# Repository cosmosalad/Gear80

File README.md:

[▶ Check Out GearSeries](https://github.com/cosmosalad/GearSeries)<br/>
[자작 과정(kr)](https://blog.naver.com/cosmosalad/223262540878)<br/><br/>

# Gear80<br/>
Gear80 is a 80% keyboard based on the rp2040.

<br/>

- gear80_wkl_Aluminum (CNC, Bead blasting-100 mesh + Anodizing-Black-Matte)

<p align="center">

</p>

<br/>

- gear80_wkl (sla print)

<br/>

- Gear80-A_1.0mm (sla print)

<br/><br/>

## Layout<br/>

- gear80 hotswap, solder

<br/>
<br/>

- gear80-a solder
<br/>
<br/>

<br/>

There is also a [keyboard plate](https://github.com/cosmosalad/Gear80/tree/main/plate).<br/>
[Keyboard case](https://github.com/cosmosalad/Gear80/tree/main/case) corresponding to this layout.<br/>

<br/><br/>

## PCB<br/>
It may differ from the sample photo and file.<br/>
<br/>
<br/>

<br/>

<br/>
<br/>
[More pcb ](https://github.com/cosmosalad/Gear80/tree/main/pcb)<br/>

This pcb was made by jlcpcb.(list of pcb parts [main](https://github.com/cosmosalad/Gear80/blob/main/pcb/Gear80%20solder/part%20list.md), [daughterboard](https://github.com/cosmosalad/Gear80/blob/main/pcb/daughterboard/part%20list.md/))<br/><br/>

This pcb prepared the [vial](https://github.com/cosmosalad/Gear80/tree/main/vial) as firmware<br/><br/><br/>

## typing sound<br/>
<p align="center">

  <br/>
Gear80 / Aluminum / HMX Hyacinth v2u / PC Plate / ABS / Full foam
<br/><br/>

  <br/>
Gear80 / Aluminum / HMX Garnet / PC Plate / ABS / no foam
<br/><br/>
  
  <br/>
Gear80 Lite / Bsun RAW /  PC Plate / ABS / Full foam
<br/><br/>
  
  <br/>
Gear80-A / sla / HMX Cheese / PC Plate / PBT / Full foam
<br/><br/>

</p>
<br/>

## Reference<br/>
- [Gear60](https://github.com/cosmosalad/Gear60)
<br/>

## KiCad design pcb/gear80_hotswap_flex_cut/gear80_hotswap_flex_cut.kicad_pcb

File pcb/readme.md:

### Gear80 hotswap<br/>
<br/>
<br/>

<br/><br/>

### Gear80 solder<br/>
<br/>
<br/>

<br/><br/>

### Gear80-A_1.0mm<br/>
<br/>
<br/>

<br/><br/>

### Gear80-A_0.5mm<br/>
<br/>
<br/>

<br/><br/>

### Gear80-daughterboard ver.0.1, ver.0.2<br/>
<br/>
<br/>

<br/><br/>

### Gear80 hotswap flex cut<br/>
<br/>
<br/>

<br/><br/>

### Gear85 hotswap flex cut, number pad<br/>
<br/>
<br/>

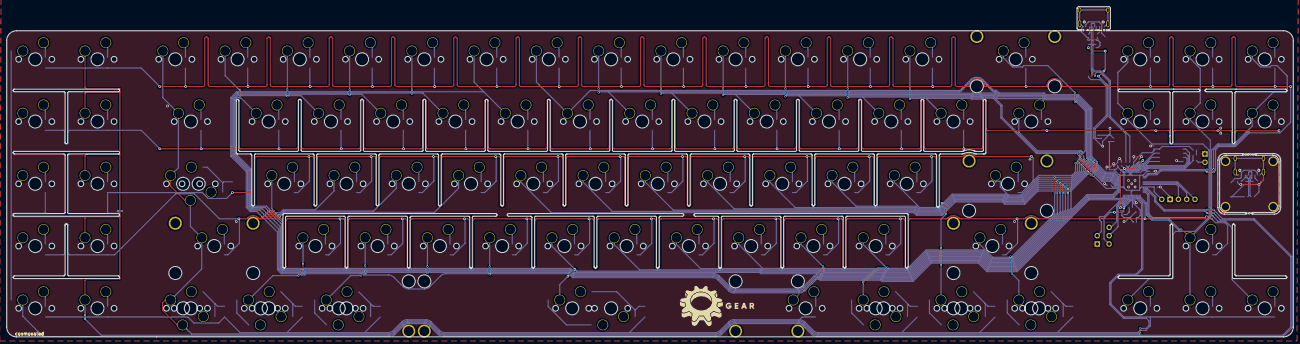
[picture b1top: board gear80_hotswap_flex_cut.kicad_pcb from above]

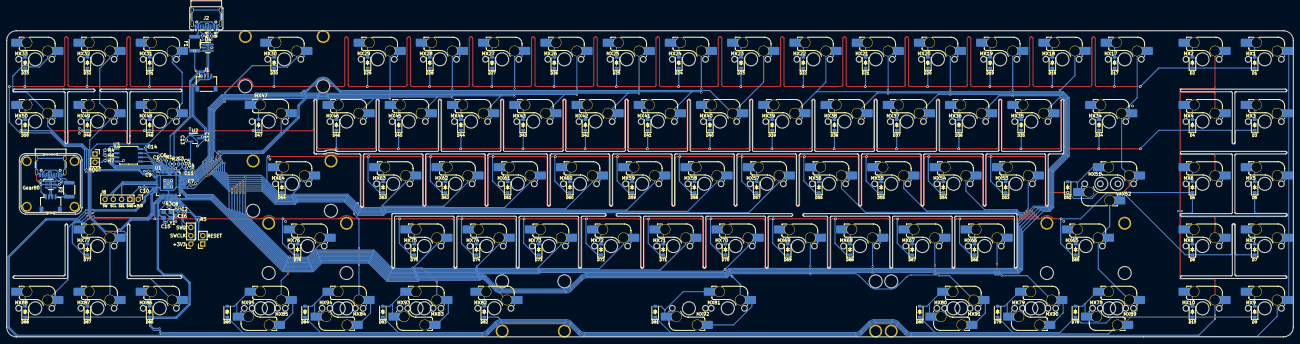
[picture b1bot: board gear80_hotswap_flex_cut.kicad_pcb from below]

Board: 2 copper layers, 393.7 x 101.0 mm, 220 parts (212 on the bottom side), 140 nets.

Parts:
BOOT1: SW_Push; PinSocket_1x02_P2.54mm_Vertical
C1, C2, C4, C5, C6, C7, C8, C9, C10: 100n; C_0402_1005Metric
C3, C11, C12, C13, C14: 1u; C_0402_1005Metric
C15, C16: 22p; C_0402_1005Metric
D1, D2, D3, D4, D5, D6, D7, D8, D9, D10, D17, D18, D19, D20, D21, D22, D23, D24, D25, D26, D27, D28, D29, D30, D31, D32, D33, D34, D35, D36, D37, D38, D39, D40, D41, D42, D43, D44, D45, D46, D47, D48, D49, D50, D51, D53, D54, D55, D56, D57, D58, D59, D60, D61, D62, D63, D64, D65, D66, D67, D68, D69, D70, D71, D72, D73, D74, D75, D76, D77, D78, D79, D80, D81, D82, D83, D84, D85, D86, D87, D88: D_Small; D_SOD-123_new
F1, F2: MF-MSMF050-2; Fuse_1812_4532Metric
GEAR: LOGO
J1, J4: Conn_01x04; JST_SH_SM04B-SRSS-TB_1x04-1MP_P1.00mm_Horizontal
J2, J5: USB_C_Receptacle_USB2.0; USB_C_Receptacle_HRO_TYPE-C-31-M-12
J3: SWD; PinSocket_1x03_P2.54mm_Vertical
J8: Conn_01x05; PinSocket_1x05_P2.54mm_Vertical
MX1, MX2, MX3, MX4, MX5, MX6, MX7, MX8, MX9, MX10, MX17, MX18, MX19, MX20, MX21, MX22, MX23, MX24, MX25, MX26, MX27, MX28, MX29, MX30, MX31, MX32, MX33, MX35, MX36, MX37, MX38, MX39, MX40, MX41, MX42, MX43, MX44, MX45, MX46, MX48, MX49, MX50, MX53, MX54, MX55, MX56, MX57, MX58, MX59, MX60, MX61, MX62, MX63, MX64, MX65, MX66, MX67, MX68, MX69, MX70, MX71, MX72, MX73, MX74, MX75, MX76, MX77, MX81, MX86, MX87, MX88, MX90, MX92, MX94: MX_SW_HS; SW_MX_HS_1u
MX34, MX47, MX89, MX91, MX93, MX95: MX_SW_HS; SW_MX_HS_1.5u
MX51: MX_SW_HS; SW_MX_HS_1.75u_STP_1.25
MX52: MX_SW_HS; SW_MX_HS_1.75u
MX78, MX79, MX80, MX82, MX83, MX84, MX85: MX_SW_HS; SW_MX_HS_1.25u
R1, R2: 27; R_0402_1005Metric
R3, R7: 1k; R_0402_1005Metric
R4, R5, R6, R8, R9, R10, R11: 5.1k; R_0402_1005Metric
RESET1: SW_Push; PinSocket_1x02_P2.54mm_Vertical
S1: stb; STAB_MX_P_2u
S3, S4: stb; STAB_MX_P_2.25u
S5: stb; STAB_MX_P_2.75u
S6: stb; STAB_MX_P_7u
S7: stb; STAB_MX_P_6.25u
U1: RP2040; QFN-56-1EP_7x7mm_P0.4mm_EP3.2x3.2mm
U2: XC6206P332MR; SOT-23-3
U3: W25Q128JVSIQ; SOIC-8_5.23x5.23mm_P1.27mm
U4, U5: SRV05-4; SOT-23-6-routable
Y1: X322512MSB4SI; Crystal_SMD_3225-4Pin_3.2x2.5mm

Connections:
+1V1: C1.1, C2.1, C3.1, U1.23 (DVDD), U1.45 (VREG_VOUT), U1.50 (DVDD)
+3V3: C4.1, C5.1, C6.1, C7.1, C8.1, C9.1, C10.1, C11.1, C13.1, C14.1, J3.1, J8.1, R4.2, R5.2, U1.1 (IOVDD), U1.10 (IOVDD), U1.22 (IOVDD), U1.33 (IOVDD), U1.42 (IOVDD), U1.43 (ADC_AVDD), U1.44 (VREG_IN), U1.48 (USB_VDD), U1.49 (IOVDD), U2.2 (VO), U3.8 (VCC)
+5V: C12.1, F1.1, J1.1, U2.3 (VI), U4.5 (VP)
+5VA: F2.1, J4.4, U5.5 (VP)
COL0: MX1.1, MX3.1, MX5.1, MX7.1, MX9.1, U1.11 (GPIO8)
COL1: MX2.1, MX4.1, MX6.1, MX8.1, MX10.1, U1.12 (GPIO9)
COL2: MX17.1, MX34.1, MX51.1, MX52.2, MX65.1, MX78.1, MX89.2, U1.18 (GPIO15)
COL3: MX18.1, MX35.1, U1.31 (GPIO20)
COL4: MX19.1, MX36.1, MX53.1, MX66.1, MX79.1, MX90.2, U1.30 (GPIO19)
COL5: MX20.1, MX37.1, MX54.1, MX67.1, MX80.1, MX91.2, U1.29 (GPIO18)
COL6: MX21.1, MX38.1, MX55.1, MX68.1, U1.28 (GPIO17)
COL7: MX22.1, MX39.1, MX56.1, MX69.1, U1.27 (GPIO16)
COL8: MX23.1, MX40.1, MX57.1, MX70.1, MX81.1, MX92.2, U1.41 (GPIO29_ADC3)
COL9: MX24.1, MX41.1, MX58.1, MX71.1, U1.40 (GPIO28_ADC2)
COL10: MX25.1, MX42.1, MX59.1, MX72.1, U1.39 (GPIO27_ADC1)
COL11: MX26.1, MX43.1, MX60.1, MX73.1, U1.38 (GPIO26_ADC0)
COL12: MX27.1, MX44.1, MX61.1, MX74.1, MX82.1, U1.37 (GPIO25)
COL13: MX28.1, MX45.1, MX62.1, MX75.1, MX83.2, MX93.1, U1.36 (GPIO24)
COL14: MX29.1, MX46.1, MX63.1, MX84.2, MX94.1, U1.35 (GPIO23)
COL15: MX30.1, MX47.1, MX64.1, MX76.1, MX85.2, MX95.1, U1.34 (GPIO22)
COL16: MX31.1, MX48.1, MX86.1, U1.15 (GPIO12)
COL17: MX32.1, MX49.1, MX77.1, MX87.1, U1.14 (GPIO11)
COL18: MX33.1, MX50.1, MX88.1, U1.13 (GPIO10)
GND: BOOT1.1, C1.2, C2.2, C3.2, C4.2, C5.2, C6.2, C7.2, C8.2, C9.2, C10.2, C11.2, C12.2, C13.2, C14.2, C15.1, C16.1, J1.4, J2.A1 (GND), J2.A12 (GND), J2.B1 (GND), J2.B12 (GND), J2.S1 (SHIELD), J8.2, R8.2, R9.2, RESET1.1, U1.19 (TESTEN), U1.57 (GND), U2.1 (GND), U3.4 (GND), U4.2 (VN), Y1.2, Y1.4
GNDA: J4.1, J5.A1 (GND), J5.A12 (GND), J5.B1 (GND), J5.B12 (GND), J5.S1 (SHIELD), R10.2, R11.2, U5.2 (VN)
GP_SCL: J8.4, U1.7 (GPIO5)
GP_SDA: J8.3, U1.8 (GPIO6)
unnamed: BOOT1.2, R7.1
unnamed: C16.2, R3.1, Y1.1
unnamed: D1.2 (A), MX1.2
unnamed: D2.2 (A), MX2.2
unnamed: D3.2 (A), MX3.2
unnamed: D4.2 (A), MX4.2
unnamed: D5.2 (A), MX5.2
unnamed: D6.2 (A), MX6.2
unnamed: D7.2 (A), MX7.2
unnamed: D8.2 (A), MX8.2
unnamed: D9.2 (A), MX9.2
unnamed: D10.2 (A), MX10.2
unnamed: D17.2 (A), MX17.2
unnamed: D18.2 (A), MX18.2
unnamed: D19.2 (A), MX19.2
unnamed: D20.2 (A), MX20.2
unnamed: D21.2 (A), MX21.2
unnamed: D22.2 (A), MX22.2
unnamed: D23.2 (A), MX23.2
unnamed: D24.2 (A), MX24.2
unnamed: D25.2 (A), MX25.2
unnamed: D26.2 (A), MX26.2
unnamed: D27.2 (A), MX27.2
unnamed: D28.2 (A), MX28.2
unnamed: D29.2 (A), MX29.2
unnamed: D30.2 (A), MX30.2
unnamed: D31.2 (A), MX31.2
unnamed: D32.2 (A), MX32.2
unnamed: D33.2 (A), MX33.2
unnamed: D34.2 (A), MX34.2
unnamed: D35.2 (A), MX35.2
unnamed: D36.2 (A), MX36.2
unnamed: D37.2 (A), MX37.2
unnamed: D38.2 (A), MX38.2
unnamed: D39.2 (A), MX39.2
unnamed: D40.2 (A), MX40.2
unnamed: D41.2 (A), MX41.2
unnamed: D42.2 (A), MX42.2
unnamed: D43.2 (A), MX43.2
unnamed: D44.2 (A), MX44.2
unnamed: D45.2 (A), MX45.2
unnamed: D46.2 (A), MX46.2
unnamed: D47.2 (A), MX47.2
unnamed: D48.2 (A), MX48.2
unnamed: D49.2 (A), MX49.2
unnamed: D50.2 (A), MX50.2
unnamed: D51.2 (A), MX51.2, MX52.1
unnamed: D53.2 (A), MX53.2
unnamed: D54.2 (A), MX54.2
unnamed: D55.2 (A), MX55.2
unnamed: D56.2 (A), MX56.2
unnamed: D57.2 (A), MX57.2
unnamed: D58.2 (A), MX58.2
unnamed: D59.2 (A), MX59.2
unnamed: D60.2 (A), MX60.2
unnamed: D61.2 (A), MX61.2
unnamed: D62.2 (A), MX62.2
unnamed: D63.2 (A), MX63.2
unnamed: D64.2 (A), MX64.2
unnamed: D65.2 (A), MX65.2
unnamed: D66.2 (A), MX66.2
unnamed: D67.2 (A), MX67.2
unnamed: D68.2 (A), MX68.2
unnamed: D69.2 (A), MX69.2
unnamed: D70.2 (A), MX70.2
unnamed: D71.2 (A), MX71.2
unnamed: D72.2 (A), MX72.2
unnamed: D73.2 (A), MX73.2
unnamed: D74.2 (A), MX74.2
unnamed: D75.2 (A), MX75.2
unnamed: D76.2 (A), MX76.2
unnamed: D77.2 (A), MX77.2
unnamed: D78.2 (A), MX78.2, MX89.1
unnamed: D79.2 (A), MX79.2, MX90.1
unnamed: D80.2 (A), MX80.2, MX91.1
unnamed: D81.2 (A), MX81.2, MX92.1
unnamed: D82.2 (A), MX82.2
unnamed: D83.2 (A), MX83.1, MX93.2
unnamed: D84.2 (A), MX84.1, MX94.2
unnamed: D85.2 (A), MX85.1, MX95.2
unnamed: D86.2 (A), MX86.2
unnamed: D87.2 (A), MX87.2
unnamed: D88.2 (A), MX88.2
unnamed: J2.A5 (CC1), R8.1
unnamed: J2.B5 (CC2), R9.1
unnamed: J5.A5 (CC1), R10.1
unnamed: J5.B5 (CC2), R11.1
unnamed: R4.1, R6.2
unnamed: R2.2, U1.46 (USB_DM)
unnamed: R1.2, U1.47 (USB_DP)
QSPI_SCLK: U1.52 (QSPI_SCLK), U3.6 (CLK)
QSPI_SD0: U1.53 (QSPI_SD0), U3.5 (DI(IO0))
QSPI_SD1: U1.55 (QSPI_SD1), U3.2 (DO(IO1))
QSPI_SD2: U1.54 (QSPI_SD2), U3.3 (IO2)
QSPI_SD3: U1.51 (QSPI_SD3), U3.7 (IO3)
QSPI_SS: R6.1, R7.2, U1.56 (QSPI_SS), U3.1 (~CS)
RESET: R5.1, RESET1.2, U1.26 (RUN)
ROW0: D1.1 (K), D2.1 (K), D17.1 (K), D18.1 (K), D19.1 (K), D20.1 (K), D21.1 (K), D22.1 (K), D23.1 (K), D24.1 (K), D25.1 (K), D26.1 (K), D27.1 (K), D28.1 (K), D29.1 (K), D30.1 (K), D31.1 (K), D32.1 (K), D33.1 (K), U1.3 (GPIO1)
ROW1: D3.1 (K), D4.1 (K), D34.1 (K), D35.1 (K), D36.1 (K), D37.1 (K), D38.1 (K), D39.1 (K), D40.1 (K), D41.1 (K), D42.1 (K), D43.1 (K), D44.1 (K), D45.1 (K), D46.1 (K), D47.1 (K), D48.1 (K), D49.1 (K), D50.1 (K), U1.2 (GPIO0)
ROW2: D5.1 (K), D6.1 (K), D51.1 (K), D53.1 (K), D54.1 (K), D55.1 (K), D56.1 (K), D57.1 (K), D58.1 (K), D59.1 (K), D60.1 (K), D61.1 (K), D62.1 (K), D63.1 (K), D64.1 (K), U1.32 (GPIO21)
ROW3: D7.1 (K), D8.1 (K), D65.1 (K), D66.1 (K), D67.1 (K), D68.1 (K), D69.1 (K), D70.1 (K), D71.1 (K), D72.1 (K), D73.1 (K), D74.1 (K), D75.1 (K), D76.1 (K), D77.1 (K), U1.16 (GPIO13)
ROW4: D9.1 (K), D10.1 (K), D78.1 (K), D79.1 (K), D80.1 (K), D81.1 (K), D82.1 (K), D83.1 (K), D84.1 (K), D85.1 (K), D86.1 (K), D87.1 (K), D88.1 (K), U1.17 (GPIO14)
SW: J8.5, U1.6 (GPIO4)
SWCLK: J3.2, U1.24 (SWCLK)
SWD: J3.3, U1.25 (SWD)
USB_D+: J1.3, J2.A6 (D+), J2.B6 (D+), R1.1, U4.1 (IO1)
USB_D+_DB: J4.2, J5.A6 (D+), J5.B6 (D+), U5.1 (IO1)
USB_D-: J1.2, J2.A7 (D-), J2.B7 (D-), R2.1, U4.6 (IO4)
USB_D-_DB: J4.3, J5.A7 (D-), J5.B7 (D-), U5.6 (IO4)
VBUS: F1.2, J2.A4 (VBUS), J2.A9 (VBUS), J2.B4 (VBUS), J2.B9 (VBUS)
VCC: F2.2, J5.A4 (VBUS), J5.A9 (VBUS), J5.B4 (VBUS), J5.B9 (VBUS)
XIN: C15.2, U1.20 (XIN), Y1.3
XOUT: R3.2, U1.21 (XOUT)

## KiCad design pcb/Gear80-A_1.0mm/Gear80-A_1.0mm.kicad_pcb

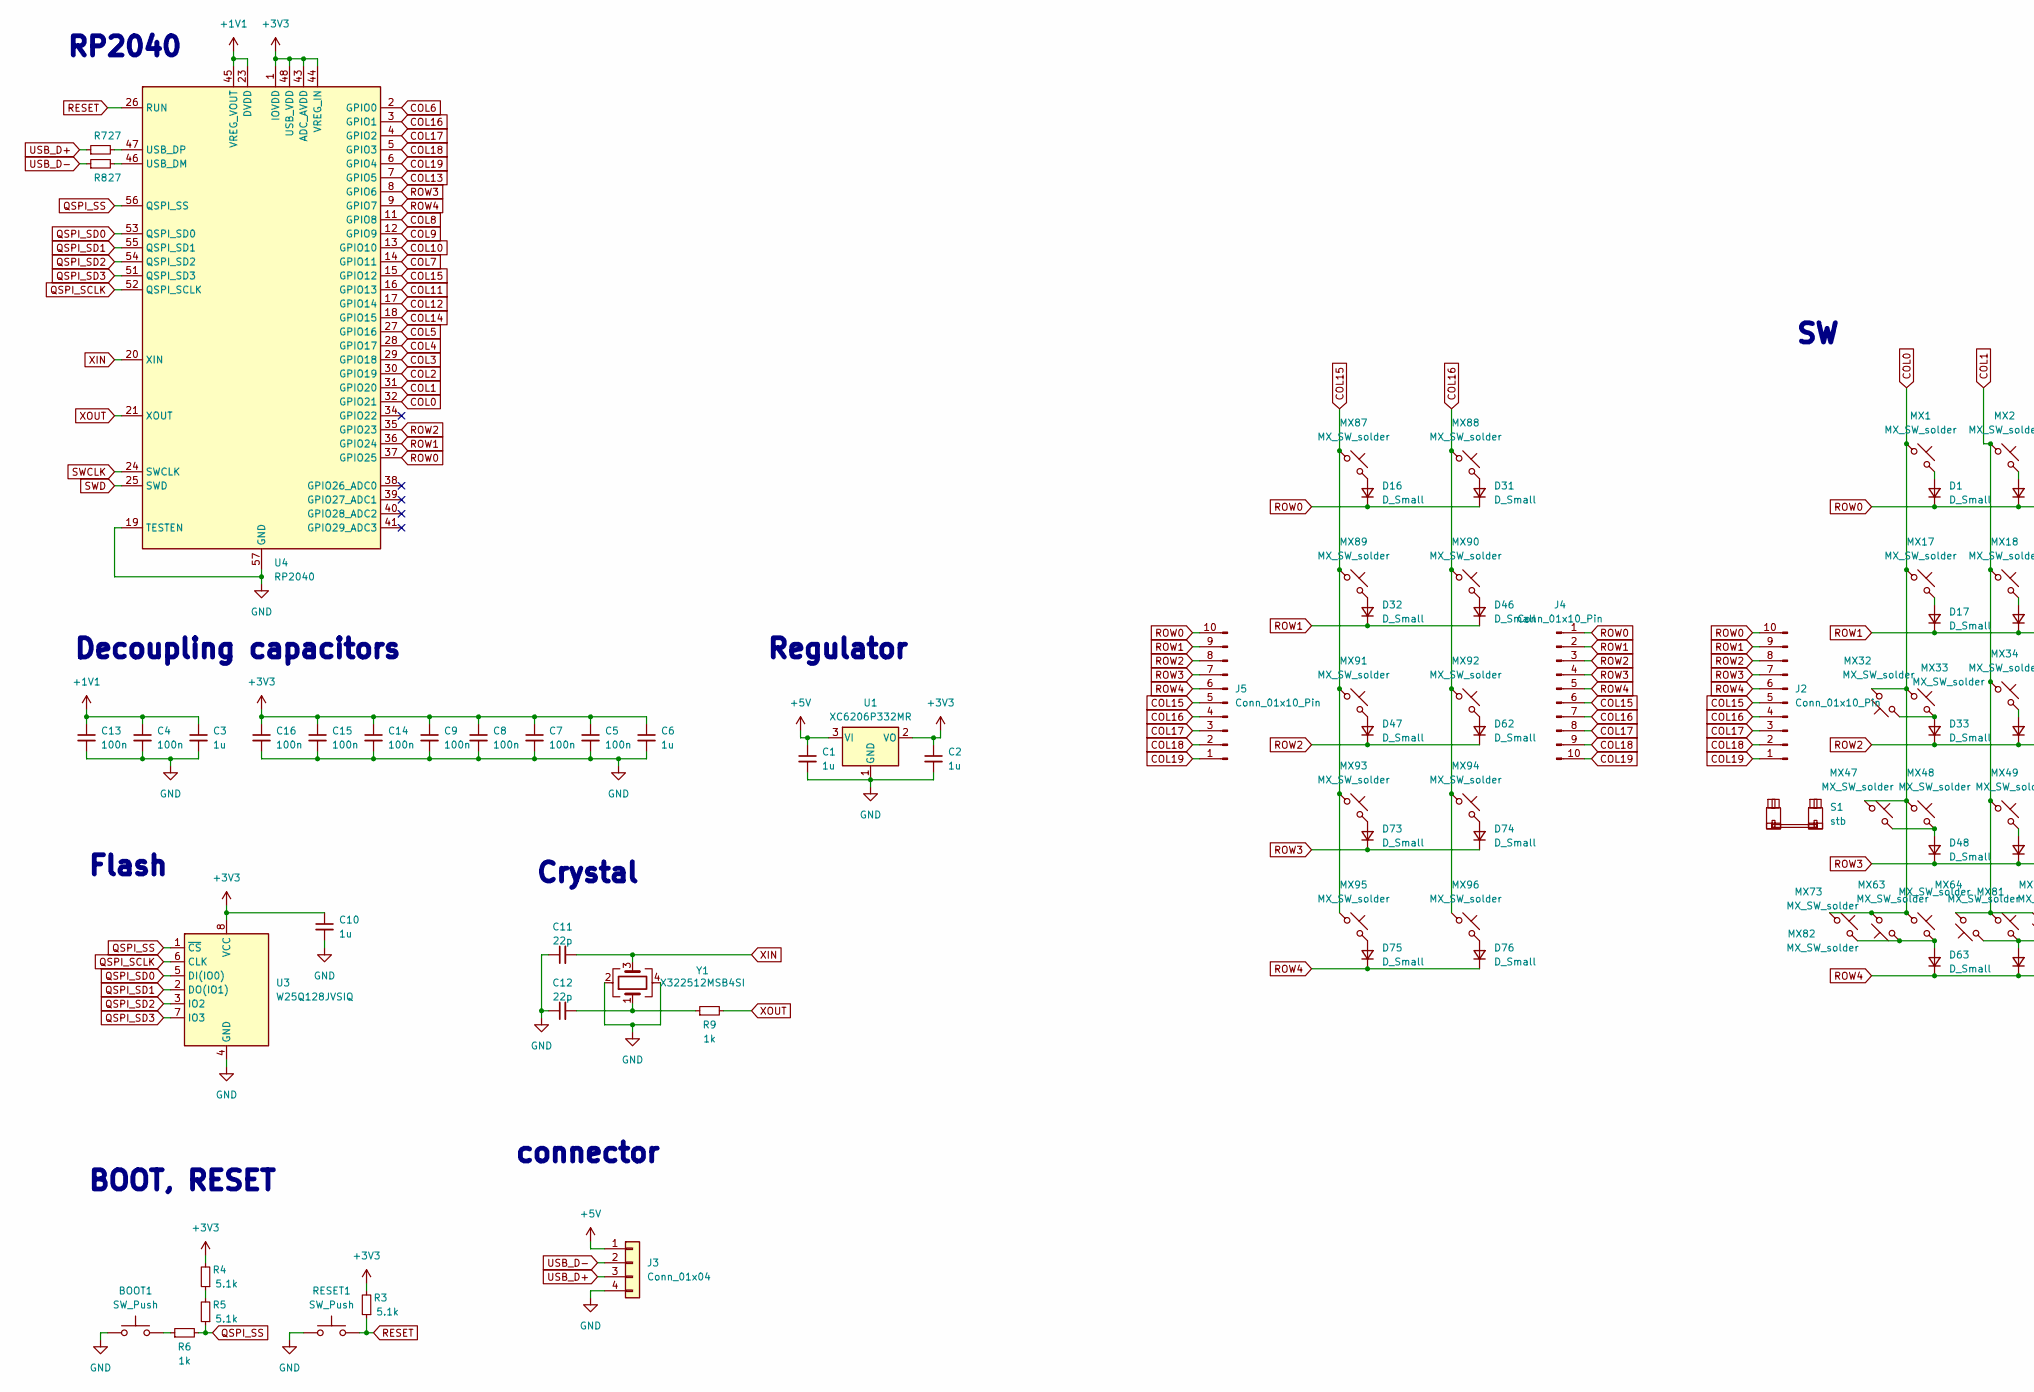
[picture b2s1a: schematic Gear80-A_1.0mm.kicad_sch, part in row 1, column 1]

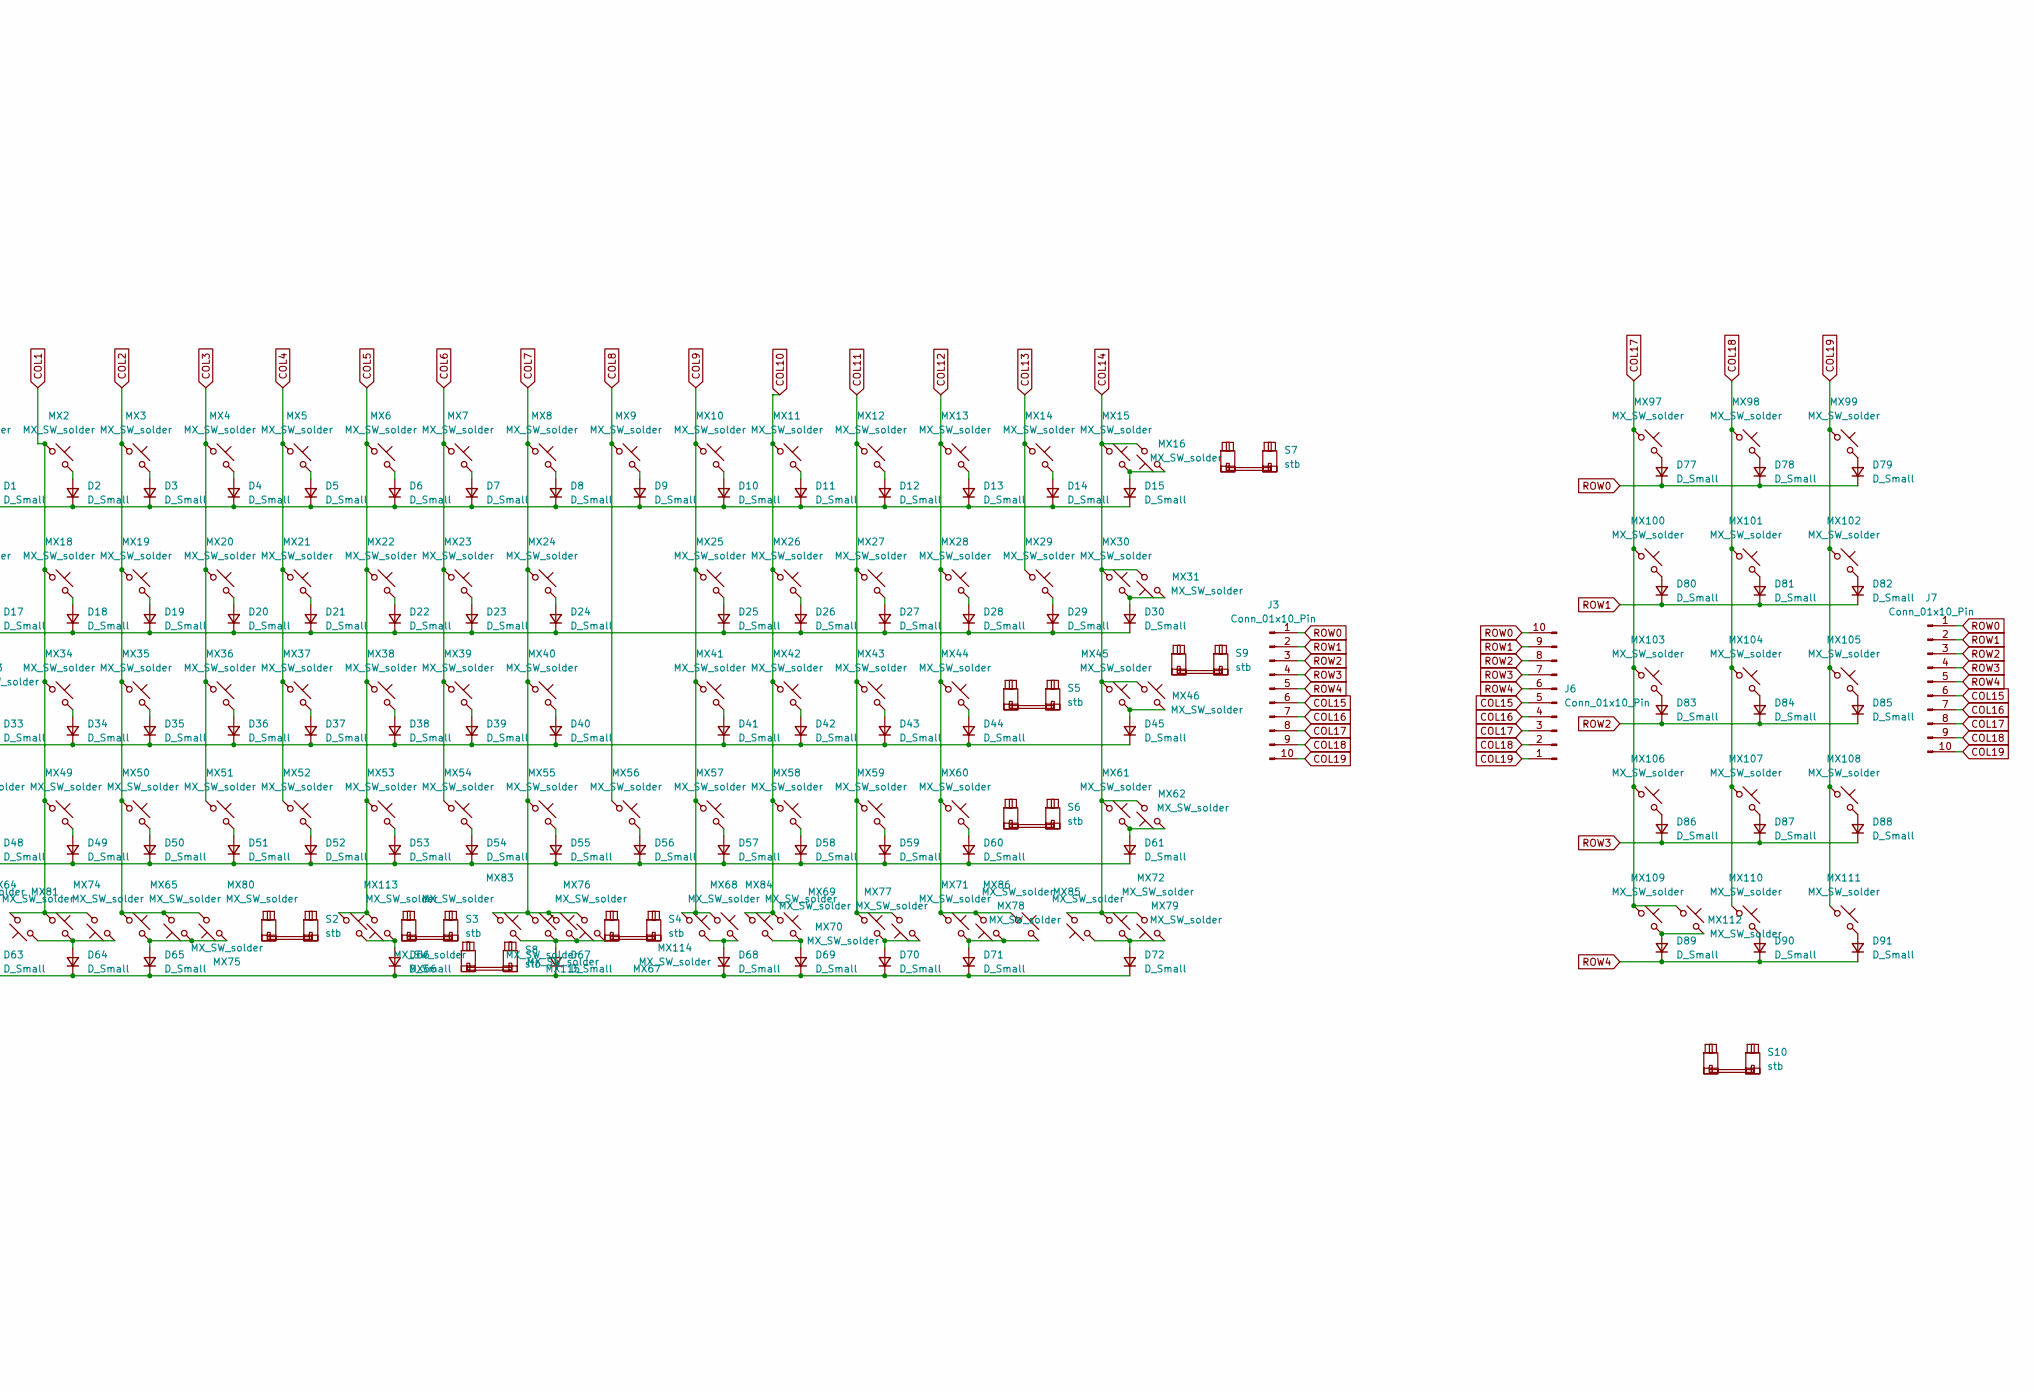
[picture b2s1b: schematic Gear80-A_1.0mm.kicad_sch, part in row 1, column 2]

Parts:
BOOT1: SW_Push; PinSocket_1x02_P2.54mm_Vertical
C1, C2, C3, C6, C10: 1u; C_0402_1005Metric
C4, C5, C7, C8, C9, C13, C14, C15, C16: 100n; C_0402_1005Metric
C11, C12: 22p; C_0402_1005Metric
D1, D2, D3, D4, D5, D6, D7, D8, D9, D10, D11, D12, D13, D14, D15, D16, D17, D18, D19, D20, D21, D22, D23, D24, D25, D26, D27, D28, D29, D30, D31, D32, D33, D34, D35, D36, D37, D38, D39, D40, D41, D42, D43, D44, D45, D46, D47, D48, D49, D50, D51, D52, D53, D54, D55, D56, D57, D58, D59, D60, D61, D62, D63, D64, D65, D66, D67, D68, D69, D70, D71, D72, D73, D74, D75, D76, D77, D78, D79, D80, D81, D82, D83, D84, D85, D86, D87, D88, D89, D90, D91: D_Small; D_SOD-123
J2, J3, J4, J5, J6, J7: Conn_01x10_Pin; Molex_200528-0100_1x10-1MP_P1.00mm_Horizontal
MX1, MX2, MX3, MX4, MX5, MX6, MX7, MX8, MX9, MX10, MX11, MX12, MX13, MX14, MX15, MX16, MX18, MX19, MX20, MX21, MX22, MX23, MX24, MX25, MX26, MX27, MX28, MX29, MX31, MX34, MX35, MX36, MX37, MX38, MX39, MX40, MX41, MX42, MX43, MX44, MX45, MX46, MX47, MX49, MX50, MX51, MX52, MX53, MX54, MX55, MX56, MX57, MX58, MX59, MX61, MX62, MX63, MX64, MX66, MX67, MX69, MX70, MX71, MX72, MX74, MX76, MX78, MX83, MX87, MX88, MX89, MX90, MX91, MX92, MX93, MX94, MX95, MX96, MX97, MX98, MX99, MX100, MX101, MX102, MX103, MX104, MX105, MX106, MX107, MX108, MX109, MX110, MX111, MX112, MX113, MX114, MX115: MX_SW_solder; SW_MX_1u
MX17, MX30, MX73, MX75, MX79: MX_SW_solder; SW_MX_1.5u
MX32: MX_SW_solder; SW_MX_1.75u_STP_1.25
MX33, MX60: MX_SW_solder; SW_MX_1.75u
MX48, MX65, MX68, MX77, MX80, MX81, MX82, MX84, MX85, MX86: MX_SW_solder; SW_MX_1.25u
R3, R4, R5: 5.1k; R_0402_1005Metric
R6, R9: 1k; R_0402_1005Metric
R7, R8: 27; R_0402_1005Metric
RESET1: SW_Push; PinSocket_1x02_P2.54mm_Vertical
S1, S3, S5: stb; STAB_MX_P_2.25u
S2, S6: stb; STAB_MX_P_2.75u
S4: stb; STAB_MX_P_7u
S7, S10: stb; STAB_MX_P_2u
S8: stb; STAB_MX_P_6.25u
S9: stb; STAB_MX_ISO
U1: XC6206P332MR; SOT-23-3
U3: W25Q128JVSIQ; SOIC-8_5.23x5.23mm_P1.27mm
U4: RP2040; QFN-56-1EP_7x7mm_P0.4mm_EP3.2x3.2mm
Y1: X322512MSB4SI; Crystal_SMD_3225-4Pin_3.2x2.5mm

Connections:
+1V1: C3.1, C4.1, C13.1, U4.23 (DVDD), U4.45 (VREG_VOUT), U4.50 (DVDD)
+3V3: C2.1, C5.1, C6.1, C7.1, C8.1, C9.1, C10.1, C14.1, C15.1, C16.1, R3.2, R4.2, U1.2 (VO), U3.8 (VCC), U4.1 (IOVDD), U4.10 (IOVDD), U4.22 (IOVDD), U4.33 (IOVDD), U4.42 (IOVDD), U4.43 (ADC_AVDD), U4.44 (VREG_IN), U4.48 (USB_VDD), U4.49 (IOVDD)
COL0: MX1.1, MX17.1, MX32.2, MX33.1, MX47.1, MX48.1, MX63.1, MX73.2, MX82.1, U4.32 (GPIO21)
COL1: MX2.1, MX18.1, MX34.1, MX49.1, MX64.1, MX74.2, MX81.2, U4.31 (GPIO20)
COL2: MX3.1, MX19.1, MX35.1, MX50.1, MX65.1, MX75.2, MX80.2, U4.30 (GPIO19)
COL3: MX4.1, MX20.1, MX36.1, MX51.1, U4.29 (GPIO18)
COL4: MX5.1, MX21.1, MX37.1, MX52.1, U4.28 (GPIO17)
COL5: MX6.1, MX22.1, MX38.1, MX53.1, MX66.2, MX113.1, U4.27 (GPIO16)
COL6: MX7.1, MX23.1, MX39.1, MX54.1, U4.2 (GPIO0)
COL7: MX8.1, MX24.1, MX40.1, MX55.1, MX67.1, MX76.1, MX83.1, MX115.2, U4.14 (GPIO11)
COL8: MX9.1, MX56.1, U4.11 (GPIO8)
COL9: MX10.1, MX25.1, MX41.1, MX57.1, MX68.1, MX114.1, U4.12 (GPIO9)
COL10: MX11.1, MX26.1, MX42.1, MX58.1, MX69.1, MX84.1, U4.13 (GPIO10)
COL11: MX12.1, MX27.1, MX43.1, MX59.1, MX70.1, MX77.2, U4.16 (GPIO13)
COL12: MX13.1, MX28.1, MX44.1, MX60.1, MX71.1, MX78.2, MX86.1, U4.17 (GPIO14)
COL13: MX14.1, MX29.1, U4.7 (GPIO5)
COL14: MX15.1, MX16.2, MX30.1, MX31.2, MX45.1, MX46.1, MX61.1, MX62.2, MX72.1, MX79.2, MX85.2, U4.18 (GPIO15)
COL15: J2.5, J3.6, J4.6, J5.5, J6.5, J7.6, MX87.1, MX89.1, MX91.1, MX93.1, MX95.1, U4.15 (GPIO12)
COL16: J2.4, J3.7, J4.7, J5.4, J6.4, J7.7, MX88.1, MX90.1, MX92.1, MX94.1, MX96.1, U4.3 (GPIO1)
COL17: J2.3, J3.8, J4.8, J5.3, J6.3, J7.8, MX97.1, MX100.1, MX103.1, MX106.1, MX109.1, MX112.1, U4.4 (GPIO2)
COL18: J2.2, J3.9, J4.9, J5.2, J6.2, J7.9, MX98.1, MX101.1, MX104.1, MX107.1, MX110.1, U4.5 (GPIO3)
COL19: J2.1, J3.10, J4.10, J5.1, J6.1, J7.10, MX99.1, MX102.1, MX105.1, MX108.1, MX111.1, U4.6 (GPIO4)
unnamed: BOOT1.2, R6.1
unnamed: C12.2, R9.1, Y1.1
unnamed: D1.2 (A), MX1.2
unnamed: D2.2 (A), MX2.2
unnamed: D3.2 (A), MX3.2
unnamed: D4.2 (A), MX4.2
unnamed: D5.2 (A), MX5.2
unnamed: D6.2 (A), MX6.2
unnamed: D7.2 (A), MX7.2
unnamed: D8.2 (A), MX8.2
unnamed: D9.2 (A), MX9.2
unnamed: D10.2 (A), MX10.2
unnamed: D11.2 (A), MX11.2
unnamed: D12.2 (A), MX12.2
unnamed: D13.2 (A), MX13.2
unnamed: D14.2 (A), MX14.2
unnamed: D15.2 (A), MX15.2, MX16.1
unnamed: D16.2 (A), MX87.2
unnamed: D17.2 (A), MX17.2
unnamed: D18.2 (A), MX18.2
unnamed: D19.2 (A), MX19.2
unnamed: D20.2 (A), MX20.2
unnamed: D21.2 (A), MX21.2
unnamed: D22.2 (A), MX22.2
unnamed: D23.2 (A), MX23.2
unnamed: D24.2 (A), MX24.2
unnamed: D25.2 (A), MX25.2
unnamed: D26.2 (A), MX26.2
unnamed: D27.2 (A), MX27.2
unnamed: D28.2 (A), MX28.2
unnamed: D29.2 (A), MX29.2
unnamed: D30.2 (A), MX30.2, MX31.1
unnamed: D31.2 (A), MX88.2
unnamed: D32.2 (A), MX89.2
unnamed: D33.2 (A), MX32.1, MX33.2
unnamed: D34.2 (A), MX34.2
unnamed: D35.2 (A), MX35.2
unnamed: D36.2 (A), MX36.2
unnamed: D37.2 (A), MX37.2
unnamed: D38.2 (A), MX38.2
unnamed: D39.2 (A), MX39.2
unnamed: D40.2 (A), MX40.2
unnamed: D41.2 (A), MX41.2
unnamed: D42.2 (A), MX42.2
unnamed: D43.2 (A), MX43.2
unnamed: D44.2 (A), MX44.2
unnamed: D45.2 (A), MX45.2, MX46.2
unnamed: D46.2 (A), MX90.2
unnamed: D47.2 (A), MX91.2
unnamed: D48.2 (A), MX47.2, MX48.2
unnamed: D49.2 (A), MX49.2
unnamed: D50.2 (A), MX50.2
unnamed: D51.2 (A), MX51.2
unnamed: D52.2 (A), MX52.2
unnamed: D53.2 (A), MX53.2
unnamed: D54.2 (A), MX54.2
unnamed: D55.2 (A), MX55.2
unnamed: D56.2 (A), MX56.2
unnamed: D57.2 (A), MX57.2
unnamed: D58.2 (A), MX58.2
unnamed: D59.2 (A), MX59.2
unnamed: D60.2 (A), MX60.2
unnamed: D61.2 (A), MX61.2, MX62.1
unnamed: D62.2 (A), MX92.2
unnamed: D63.2 (A), MX63.2, MX73.1, MX82.2
unnamed: D64.2 (A), MX64.2, MX74.1, MX81.1
unnamed: D65.2 (A), MX65.2, MX75.1, MX80.1
unnamed: D66.2 (A), MX66.1, MX113.2
unnamed: D67.2 (A), MX67.2, MX76.2, MX83.2, MX115.1
unnamed: D68.2 (A), MX68.2, MX114.2
unnamed: D69.2 (A), MX69.2, MX84.2
unnamed: D70.2 (A), MX70.2, MX77.1
unnamed: D71.2 (A), MX71.2, MX78.1, MX86.2
unnamed: D72.2 (A), MX72.2, MX79.1, MX85.1
unnamed: D73.2 (A), MX93.2
unnamed: D74.2 (A), MX94.2
unnamed: D75.2 (A), MX95.2
unnamed: D76.2 (A), MX96.2
unnamed: D77.2 (A), MX97.2
unnamed: D78.2 (A), MX98.2
unnamed: D79.2 (A), MX99.2
unnamed: D80.2 (A), MX100.2
unnamed: D81.2 (A), MX101.2
unnamed: D82.2 (A), MX102.2
unnamed: D83.2 (A), MX103.2
unnamed: D84.2 (A), MX104.2
unnamed: D85.2 (A), MX105.2
unnamed: D86.2 (A), MX106.2
unnamed: D87.2 (A), MX107.2
unnamed: D88.2 (A), MX108.2
unnamed: D89.2 (A), MX109.2, MX112.2
unnamed: D90.2 (A), MX110.2
unnamed: D91.2 (A), MX111.2
unnamed: R4.1, R5.2
unnamed: R8.2, U4.46 (USB_DM)
unnamed: R7.2, U4.47 (USB_DP)
QSPI_SCLK: U3.6 (CLK), U4.52 (QSPI_SCLK)
QSPI_SD0: U3.5 (DI(IO0)), U4.53 (QSPI_SD0)
QSPI_SD1: U3.2 (DO(IO1)), U4.55 (QSPI_SD1)
QSPI_SD2: U3.3 (IO2), U4.54 (QSPI_SD2)
QSPI_SD3: U3.7 (IO3), U4.51 (QSPI_SD3)
QSPI_SS: R5.1, R6.2, U3.1 (~CS), U4.56 (QSPI_SS)
RESET: R3.1, RESET1.2, U4.26 (RUN)
ROW4: D63.1 (K), D64.1 (K), D65.1 (K), D66.1 (K), D67.1 (K), D68.1 (K), D69.1 (K), D70.1 (K), D71.1 (K), D72.1 (K), D75.1 (K), D76.1 (K), D89.1 (K), D90.1 (K), D91.1 (K), J2.6, J3.5, J4.5, J5.6, J6.6, J7.5, U4.9 (GPIO7)
SWCLK: U4.24 (SWCLK)
SWD: U4.25 (SWD)
XIN: C11.2, U4.20 (XIN), Y1.3
XOUT: R9.2, U4.21 (XOUT)

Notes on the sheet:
BOOT, RESET
Decoupling capacitors
RP2040
connector
Crystal
Regulator
Flash

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
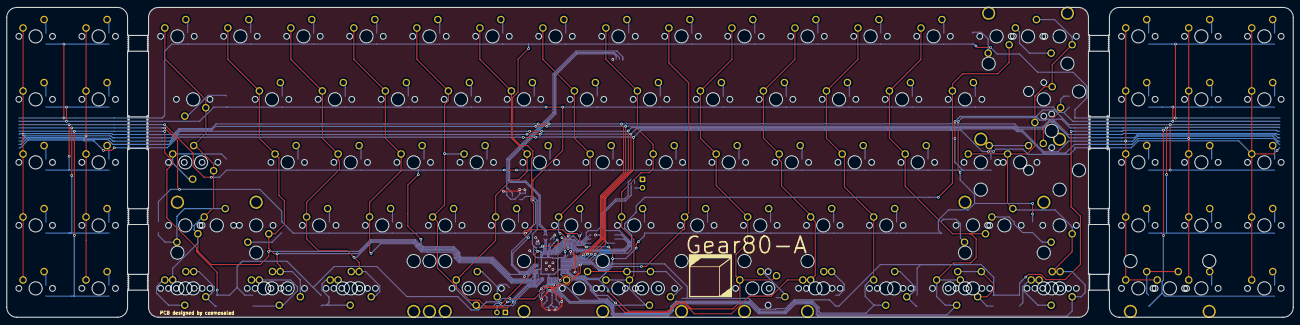
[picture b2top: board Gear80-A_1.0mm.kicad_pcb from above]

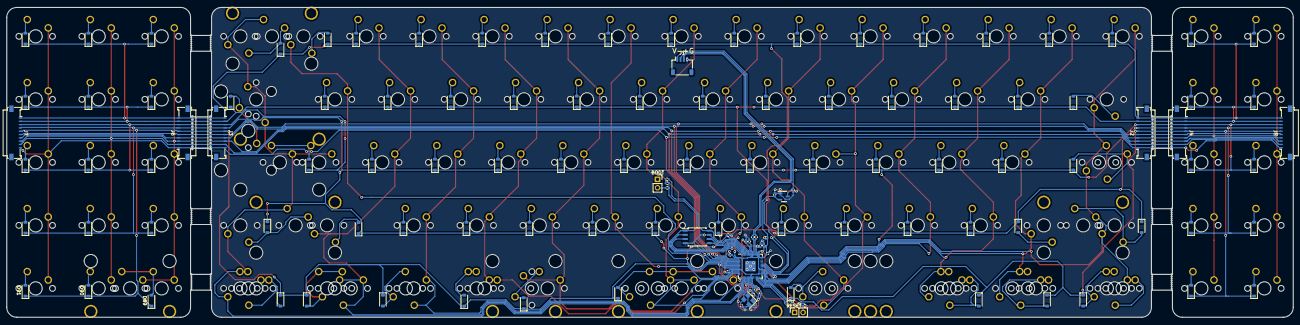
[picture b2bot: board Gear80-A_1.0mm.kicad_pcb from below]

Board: 2 copper layers, 388.9 x 93.7 mm, 252 parts (127 on the bottom side), 136 nets.

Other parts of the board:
J1: Conn_01x04; JST_SH_SM04B-SRSS-TB_1x04-1MP_P1.00mm_Horizontal

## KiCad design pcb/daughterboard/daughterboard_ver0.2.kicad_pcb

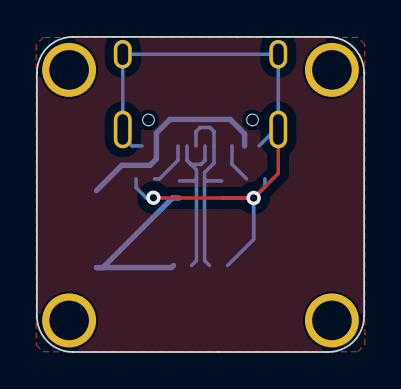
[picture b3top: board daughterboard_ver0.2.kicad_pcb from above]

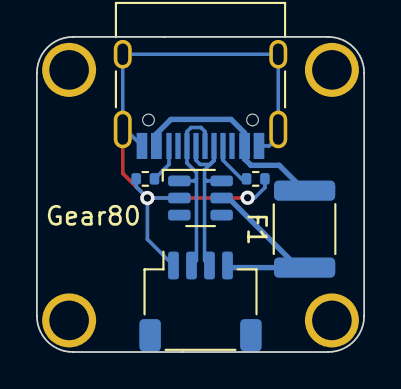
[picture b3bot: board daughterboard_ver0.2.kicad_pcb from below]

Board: 2 copper layers, 18.2 x 17.5 mm, 6 parts (6 on the bottom side), 7 nets.

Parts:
F1: MF-MSMF050-2; Fuse_1812_4532Metric
J1: Conn_01x04; JST_SH_SM04B-SRSS-TB_1x04-1MP_P1.00mm_Horizontal
J2: USB_C_Receptacle_USB2.0; USB_C_Receptacle_HRO_TYPE-C-31-M-12
R1, R2: 5.1k; R_0402_1005Metric
U1: SRV05-4; SOT-23-6-routable

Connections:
+5V: F1.1, J1.4, U1.5 (VP)
GND: J1.1, J2.A1 (GND), J2.A12 (GND), J2.B1 (GND), J2.B12 (GND), J2.S1 (SHIELD), R1.2, R2.2, U1.2 (VN)
unnamed: J2.A5 (CC1), R1.1
unnamed: J2.B5 (CC2), R2.1
USB_D+: J1.2, J2.A6 (D+), J2.B6 (D+), U1.1 (IO1)
USB_D-: J1.3, J2.A7 (D-), J2.B7 (D-), U1.6 (IO4)
VBUS: F1.2, J2.A4 (VBUS), J2.A9 (VBUS), J2.B4 (VBUS), J2.B9 (VBUS)

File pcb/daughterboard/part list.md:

|       **Comment**       | **Designator** |                          **Footprint**                         | **JLCPCB Part #** |
|:-----------------------:|:--------------:|:--------------------------------------------------------------:|:-----------------:|
| USB_C_Receptacle_USB2.0 | J2             | Connector_USB:USB_C_Receptacle_HRO_TYPE-C-31-M-12              | C165948           |
| MF-MSMF050-2 500mA       | F1             | Fuse:Fuse_2010_5025Metric                                      | C17313            |
| 5.1k                    | R1,R2          | Resistor_SMD:R_0402_1005Metric                                 | C25905            |
| Conn_01x04              | J1             | Connector_JST:JST_SH_SM04B-SRSS-TB_1x04-1MP_P1.00mm_Horizontal | C2845363          |
| SRV05-4                 | U1             | PCM_marbastlib-various:SOT-23-6-routable                       | C7420376          |

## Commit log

2024-03-08 Create ;
2024-03-08 Rename case_part.stl to sla_part.stl
2024-03-09 Rename gear80-A_vial.uf2 to gear80-a_vial.uf2
2024-03-09 Create LICENSE
2024-03-09 Create Gear80_hotswap
2024-03-09 Create Gear80_solder
2024-07-16 Rename daughterboard.kicad_pro to daughterboard_ver0.1.kicad_pro
